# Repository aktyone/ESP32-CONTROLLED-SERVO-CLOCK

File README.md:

# ESP32-CONTROLLED-SERVO-CLOCK
Servo digital clock controlled via an esp32 connected to wifi to get the real life time
https://cad.onshape.com/documents/a1e01fce5c0e03bf5ce65987/w/6e7c594a7fabd89bfe559070/e/7c6dac26cfcae9382fc0ca5d

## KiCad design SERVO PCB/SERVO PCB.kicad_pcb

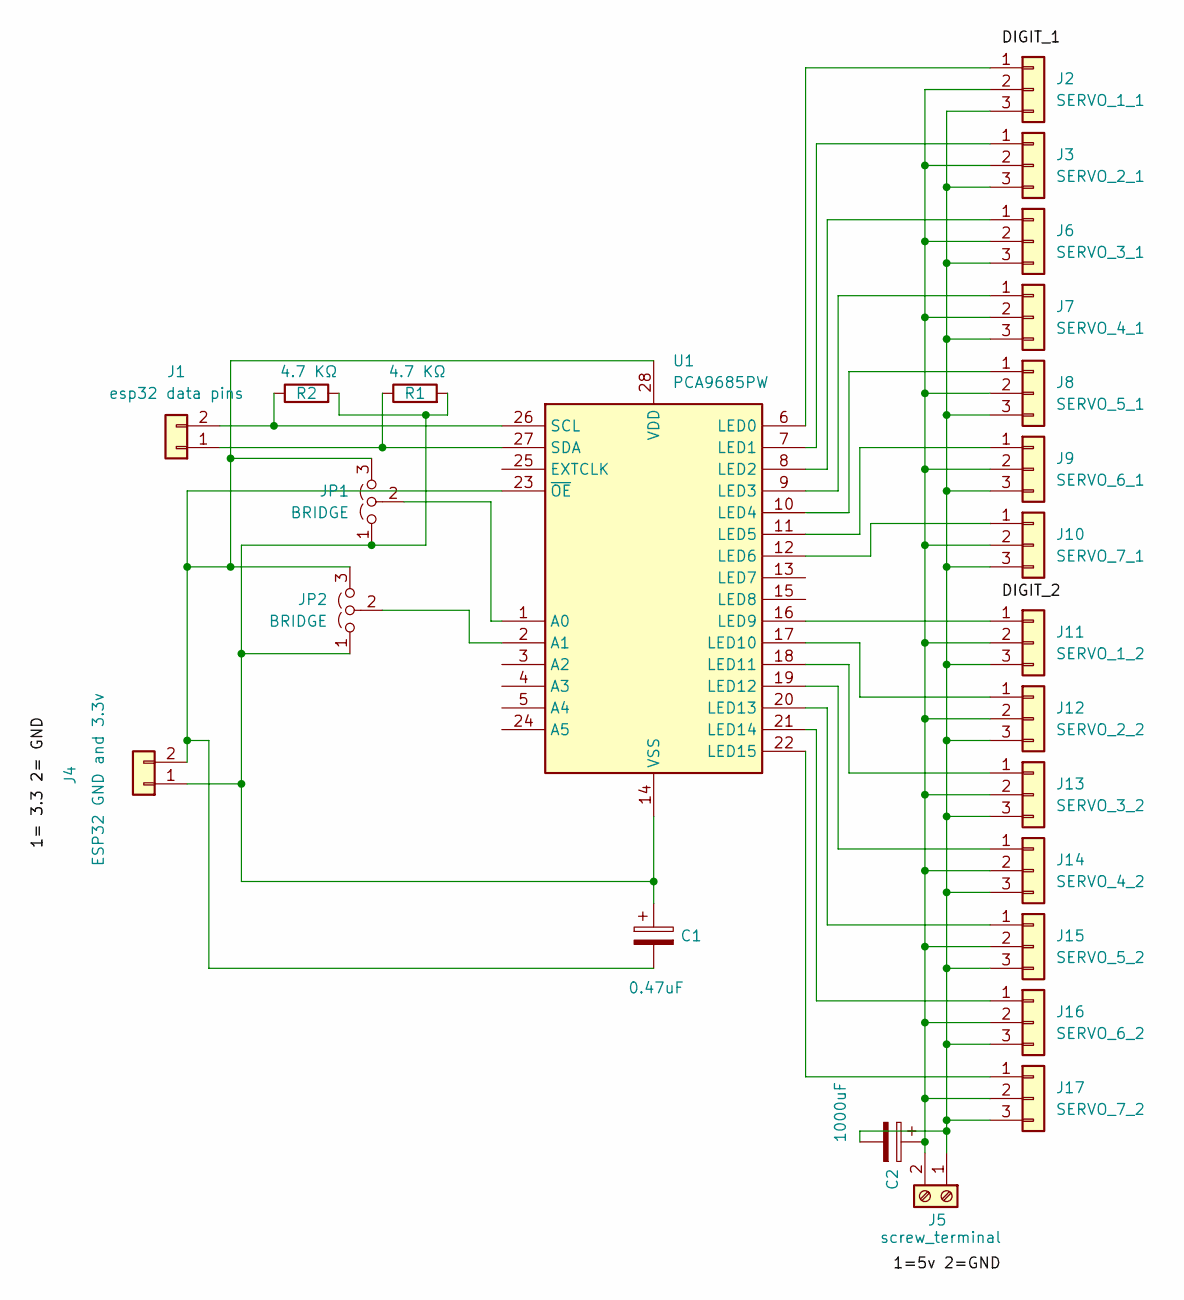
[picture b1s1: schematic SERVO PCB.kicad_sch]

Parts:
C1: 0.47uF; CP_Radial_D4.0mm_P2.00mm
C2: 1000uF; CP_Radial_D13.0mm_P7.50mm
J1: esp32 data pins; PinHeader_1x02_P2.54mm_Vertical
J2: SERVO_1_1; PinHeader_1x03_P2.54mm_Vertical
J3: SERVO_2_1; PinHeader_1x03_P2.54mm_Vertical
J4: ESP32 GND and 3.3v; PinHeader_1x02_P2.54mm_Vertical
J5: screw_terminal; TerminalBlock_Phoenix_MKDS-1,5-2_1x02_P5.00mm_Horizontal
J6: SERVO_3_1; PinHeader_1x03_P2.54mm_Vertical
J7: SERVO_4_1; PinHeader_1x03_P2.54mm_Vertical
J8: SERVO_5_1; PinHeader_1x03_P2.54mm_Vertical
J9: SERVO_6_1; PinHeader_1x03_P2.54mm_Vertical
J10: SERVO_7_1; PinHeader_1x03_P2.54mm_Vertical
J11: SERVO_1_2; PinHeader_1x03_P2.54mm_Vertical
J12: SERVO_2_2; PinHeader_1x03_P2.54mm_Vertical
J13: SERVO_3_2; PinHeader_1x03_P2.54mm_Vertical
J14: SERVO_4_2; PinHeader_1x03_P2.54mm_Vertical
J15: SERVO_5_2; PinHeader_1x03_P2.54mm_Vertical
J16: SERVO_6_2; PinHeader_1x03_P2.54mm_Vertical
J17: SERVO_7_2; PinHeader_1x03_P2.54mm_Vertical
JP1, JP2: BRIDGE; SolderJumper-3_P1.3mm_Open_Pad1.0x1.5mm
R1, R2: 4.7 KΩ; R_Axial_DIN0207_L6.3mm_D2.5mm_P7.62mm_Horizontal
U1: PCA9685PW; TSSOP-28_4.4x9.7mm_P0.65mm

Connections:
unnamed: J1.1, R1.1, U1.27 (SDA)
unnamed: J1.2, R2.1, U1.26 (SCL)
unnamed: J2.1, U1.6 (LED0)
unnamed: J3.1, U1.7 (LED1)
unnamed: C1.1, J4.1, JP1.1 (A), JP2.1 (A), R1.2, R2.2, U1.14 (VSS)
unnamed: C1.2, J4.2, JP1.3 (B), JP2.3 (B), U1.23 (~OE), U1.28 (VDD)
unnamed: J6.1, U1.8 (LED2)
unnamed: J7.1, U1.9 (LED3)
unnamed: J8.1, U1.10 (LED4)
unnamed: J9.1, U1.11 (LED5)
unnamed: J10.1, U1.12 (LED6)
unnamed: C2.1, J2.2, J3.2, J5.2, J6.2, J7.2, J8.2, J9.2, J10.2, J11.2, J12.2, J13.2, J14.2, J15.2, J16.2, J17.2
unnamed: C2.2, J2.3, J3.3, J5.1, J6.3, J7.3, J8.3, J9.3, J10.3, J11.3, J12.3, J13.3, J14.3, J15.3, J16.3, J17.3
unnamed: J11.1, U1.16 (LED9)
unnamed: J12.1, U1.17 (LED10)
unnamed: J13.1, U1.18 (LED11)
unnamed: J14.1, U1.19 (LED12)
unnamed: J15.1, U1.20 (LED13)
unnamed: J16.1, U1.21 (LED14)
unnamed: J17.1, U1.22 (LED15)
unnamed: JP1.2 (C), U1.1 (A0)
unnamed: JP2.2 (C), U1.2 (A1)

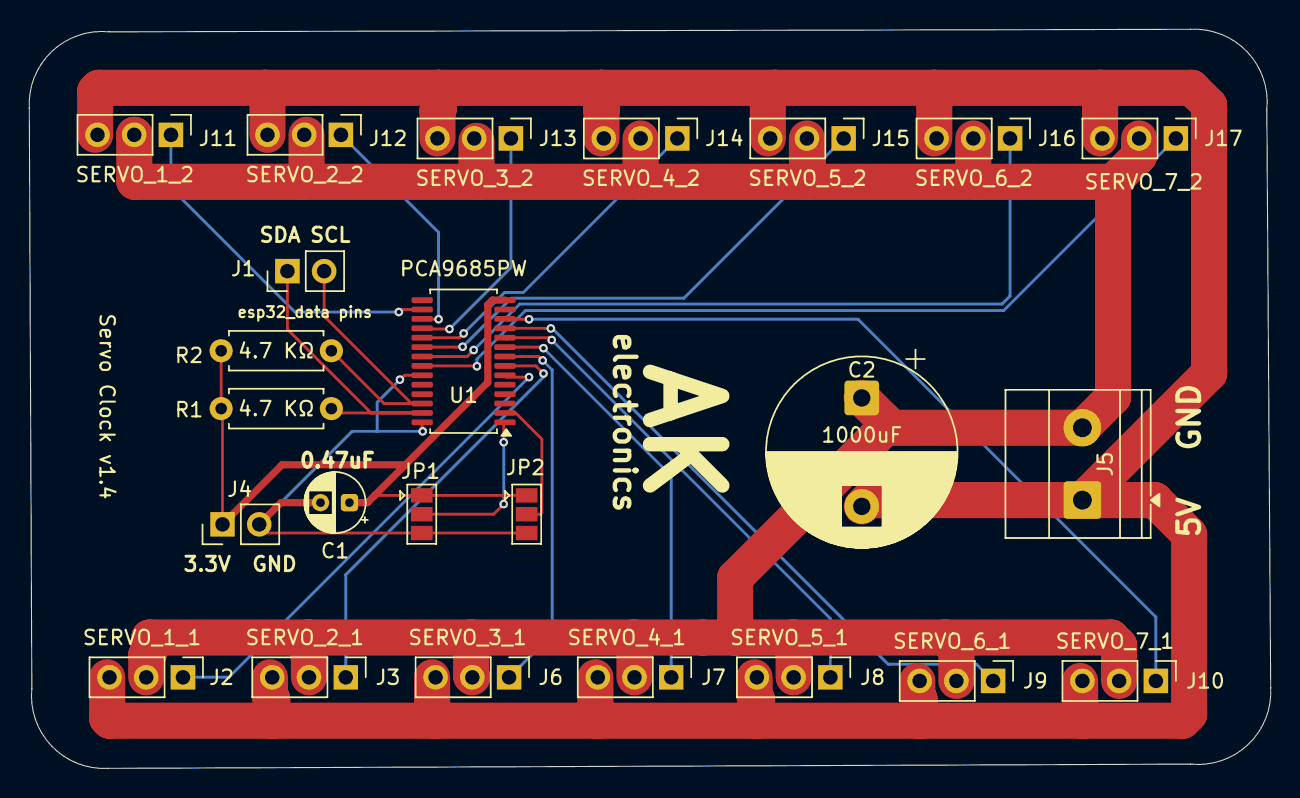
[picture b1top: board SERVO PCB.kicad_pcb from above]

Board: 2 copper layers, 85.8 x 51.1 mm, 24 parts (0 on the bottom side), 22 nets.
